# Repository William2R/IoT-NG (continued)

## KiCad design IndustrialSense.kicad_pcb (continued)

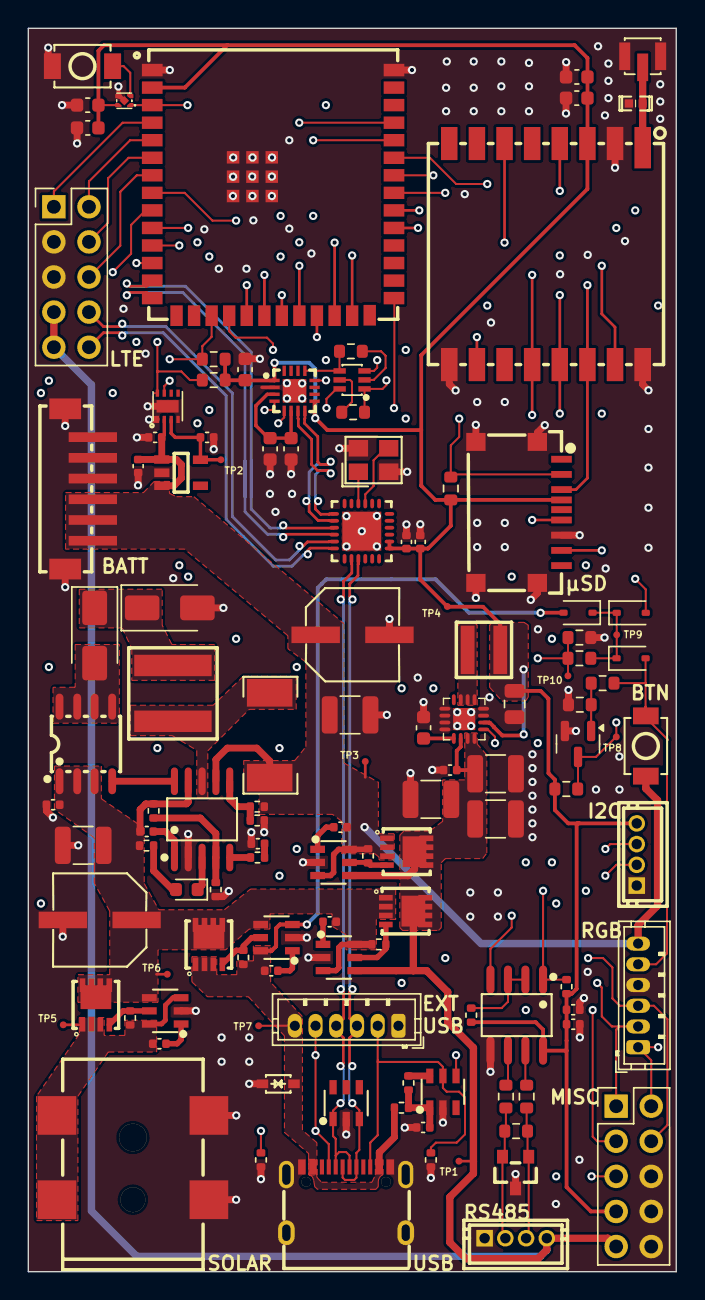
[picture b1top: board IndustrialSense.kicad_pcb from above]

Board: 4 copper layers, 46.9 x 90.0 mm, 120 parts (0 on the bottom side), 86 nets.

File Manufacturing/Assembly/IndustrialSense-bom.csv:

Row,Quantity Per PCB,References,Value,Datasheet,Footprint,Description,Manufacturer,Manufacturer Part Number,Supplier Part Number
1,1,C16,3.3n,~,C_0603_1608Metric,Unpolarized capacitor,,,
2,14,C5 C12 C15 C17 C18 C19 C20 C22 C24 C26 C40 C43 C44 C48,100n,~,C_0402_1005Metric,Unpolarized capacitor,,,
3,1,C25,220n,~,C_0402_1005Metric,Unpolarized capacitor,,,
4,5,C37 C38 C39 C46 C47,1u,~,C_0402_1005Metric,Unpolarized capacitor,,,
5,6,C14 C21 C23 C41 C42 C45,10u,~,C_1210_3225Metric,Unpolarized capacitor,,,
6,1,C13,22u,~,C_0805_2012Metric,Unpolarized capacitor,,,
7,2,C1 C7,47u,https://lcsc.com/product-detail/Aluminum-Electrolytic-Capaci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,CAP-SMD_BD6.3-L6.6-W6.6-LS7.6-FD,,,,
8,2,C4 C6,100u,~,C_1210_3225Metric,Unpolarized capacitor,,,
9,2,CN2 CN4,B4B-ZR (LF)(SN),https://lcsc.com/product-detail/Connectors_JST_B4B-ZR-LF-SN_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,CONN-TH_B4B-ZR-LF-SN,,,,
10,1,CN3,ZH1.5-6P-LT,https://lcsc.com/product-detail/Wire-To-Board-Wire-To-Wire-C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,CONN-SMD_ZH1.5-6P-LT,,,,
11,1,Card1,XKTF-0803-0,https://lcsc.com/product-detail/Connector-Card-Sockets_XKB-E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,TF-SMD_XKTF-0803-0,,,,
12,3,D6 D7 D8,1N5819WS,https://datasheet.lcsc.com/lcsc/2204281430_Guangdong-Hottech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,D_SOD-323,"40V 600mV@1A 1A SOD-323 Schottky Barrier Diodes, SOD-323",,,
13,1,D4,BV24C,,SOD-323_L1.7-W1.3-LS2.6-BI,,,,
14,1,D10,CDSOT23-SM712,https://lcsc.com/product-detail/Diodes-ESD_BOURNS-CDSOT23-SM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,SOT-23_L2.9-W1.3-P1.90-LS2.4-BR,,,,
15,1,D5,DT1042-04SO-7,https://lcsc.com/product-detail/TVS_Diodes-Incorporated-DT10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,SOT-26_L3.0-W1.6-P0.95-LS2.8-BL,,,,
16,1,D3,PESD0402-140,https://lcsc.com/product-detail/TVS_TE-Connectivity_PESD0402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,D0402-BI,,,,
17,2,D1 D2,SS24,https://www.vishay.com/docs/88748/ss22.pdf,D_SMA,"40V 2A Schottky Diode, SMA",,,
18,1,D16,WHITE2,~,LED_0603_1608Metric,Light emitting diode,,,
19,1,DC1,DC-005-5A-2.0-SMT,https://lcsc.com/product-detail/Power-Connectors_XKB-Enterpr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,DC-IN-TH_DC-005-5A-2.0-SMT,,,,
20,2,J5 J6,Conn_01x10_Socket,~,PinHeader_2x05_P2.54mm_Vertical,"Generic connector, single row, 01x10, script generated",,,
21,1,L2,RA-01SH,,WIRELM-SMD_RA-01SH,,,,
22,1,L3,XAL6060-223MEC,,IND-SMD_L6.6-W6.4,,,,
23,1,Q5,CEM4435A,https://lcsc.com/product-detail/MOSFET_VBsemi-Elec-CEM4435A_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,SO-8_L4.9-W3.9-P1.27-LS5.9-BL,,,,
24,1,Q6,CH221K,,SOT-23-6_L2.9-W1.6-P0.95-LS2.8-BL-2,,,,
25,1,Q15,LMBT3904DW1T1G,https://lcsc.com/product-detail/Transistors-NPN-PNP_LMBT3904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,SOT-363_L2.0-W1.3-P0.65-LS2.1-BR,,,,
26,1,Q13,MMBT3904,https://www.onsemi.com/pdf/datasheet/pzt3904-d.pdf,SOT-23,"0.2A Ic, 40V Vce, Small Signal NPN Transistor, SOT-23",,,
27,4,Q1 Q2 Q3 Q4,SISA14DN-T1-GE3,,POWERPAK-1212-8_L3.3-W3.1-P0.65-BL-EP,,,,
28,1,R8,50m,,RES-SMD_L6.4-W3.2-R2512,,,,
29,2,R67 R68,10,~,R_0603_1608Metric,"Resistor, US symbol",,,
30,2,R7 R69,120,~,R_0402_1005Metric,"Resistor, US symbol",,,
31,2,R11 R60,1k,~,R_0402_1005Metric,"Resistor, US symbol",,,
32,2,R4 R5,5.1k,~,R_0402_1005Metric,"Resistor, US symbol",,,
33,6,R18 R19 R53 R54 R57 R58,10k,~,R_0402_1005Metric,"Resistor, US symbol",,,
34,3,R47 R48 R59,47k,~,R_0603_1608Metric,"Resistor, US symbol",,,
35,1,R13,78.7k,~,R_0402_1005Metric,"Resistor, US symbol",,,
36,4,R10 R49 R50 R56,100k,~,R_0402_1005Metric,"Resistor, US symbol",,,
37,1,R55,150k,~,R_0603_1608Metric,"Resistor, US symbol",,,
38,1,R12,470k,~,R_0402_1005Metric,"Resistor, US symbol",,,
39,1,R9,820k,~,R_0402_1005Metric,"Resistor, US symbol",,,
40,4,R1 R2 R3 R6,1M,~,R_0402_1005Metric,"Resistor, US symbol",,,
41,1,RF1,CONUFL001-SMD-T,,IPEX-SMD_3P-L2.6-W2.6-LS3.0,,,,
42,2,SW2 SW3,SKRKAEE020,https://lcsc.com/product-detail/Tactile-Switches_ALPS_SKRKAE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,SW-SMD_L3.9-W3.0-P4.45,,,,
43,2,U2 U13,B6B-ZR (LF)(SN),https://lcsc.com/product-detail/_JST-Sales-America__JST-Sale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,CONN-TH-6P-P1.50_B6B-ZR-LF-SN,,,,
44,1,U14,CH334F,,QFN-24_L4.0-W4.0-P0.50-BL-EP2.8,,,,
45,1,U3,CH343P,,TQFN-16_L3.0-W3.0-P0.50-BL-EP1.7,,,,
46,1,U11,CN3795,https://lcsc.com/product-detail/Others_ShangHai-Consonance-E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,SSOP-10_L4.9-W3.9-P1.00-LS6.0-BL,,,,
47,1,U1,ESP32-S3-WROOM-1U-N16,,WIRELM-SMD_ESP32-S3-WROOM-1U,,,,
48,4,U5 U6 U8 U10,LM74700QDBVRQ1,,SOT-23-6_L2.9-W1.6-P0.95-LS2.8-BL,,,,
49,1,U4,MAX17049G+T10,,WSON-8_L2.0-W2.0-P0.50-BL-EP0.9,,,,
50,1,U17,THVD1406DR,,SOIC-8_L4.9-W3.9-P1.27-LS6.0-BL,,,,
51,1,U15,TPS3831G33DQNR,,X2SON-4_L1.0-W1.0-P0.65-TL-EP,,,,
52,1,U7,TPS62132RGTT,,VQFN-16_L3.0-W3.0-P0.50-TL-EP,,,,
53,1,U9,XC6209F332MR-G,https://lcsc.com/product-detail/Others_Torex-Semicon-XC6209F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,SOT-25-5_L3.0-W1.8-P0.95-LS3.0-BR,,,,
54,1,U12,XFL4020-222MEC_C122469,,IND-SMD_L4.0-W4.0_XAL4030-332MEC,,,,
55,1,USB1,TYPE-C 16PIN 2MD(073),,USB-C-SMD_TYPE-C-6PIN-2MD-073,,,,
56,1,X1,X322512MSB4SI,https://lcsc.com/product-detail/SMD-Crystals_YSX321SL-12MHZ-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,CRYSTAL-SMD_4P-L3.2-W2.5-BL,,,,

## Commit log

2026-02-21 Initial commit: base files of the project
2026-02-21 First draft of the schematic
2026-02-21 Update Outputs
2026-02-21 [Schematic][Added] Project Architecture, connectors
2026-02-22 [Schematic][Added] Net labels
2026-02-23 [PCB/SCH][Added] Preliminary version
2026-02-24 [Schematic][Added] Connectors and first PCB layout
2026-02-25 [Schematic/PCB][Added] Connectors, layout, preliminar routing
2026-02-26 [Schematic/PCB][Added] Routing almost finished
2026-02-26 [Schematic/PCB][Added] Routing finished, DRC finished
2026-02-27 [Schematic/PCB][Added] Testpoints and fabrication files test
2026-02-27 [Schematic/PCB][Added] Testpoints test 2
2026-02-27 [Schematic/PCB][Added] Testpoints test 3
2026-02-27 [PCB] Checked
2026-02-28 [PCB][Added] Gerber, CPL, BOM ready
2026-02-28 Update CHANGELOG
2026-02-28 Update Outputs (release)
2026-03-03 Update LICENSE
